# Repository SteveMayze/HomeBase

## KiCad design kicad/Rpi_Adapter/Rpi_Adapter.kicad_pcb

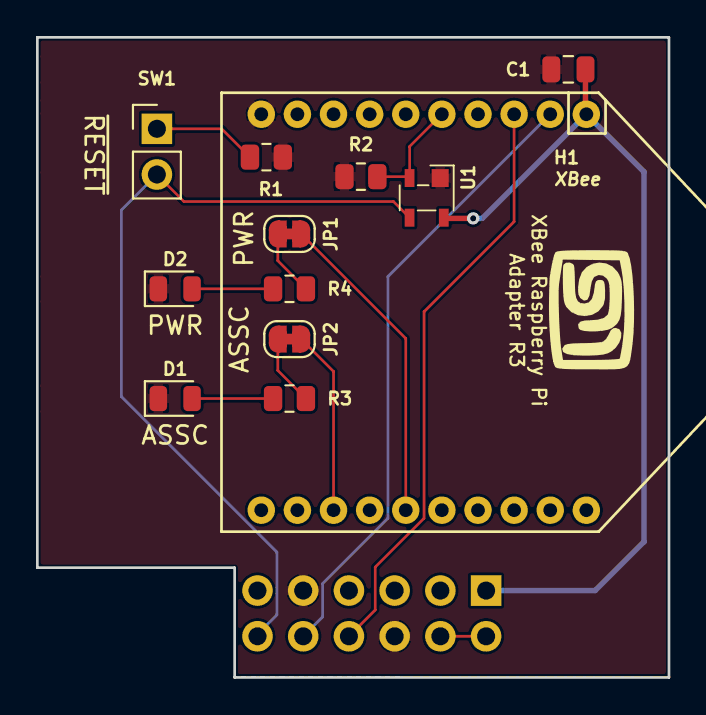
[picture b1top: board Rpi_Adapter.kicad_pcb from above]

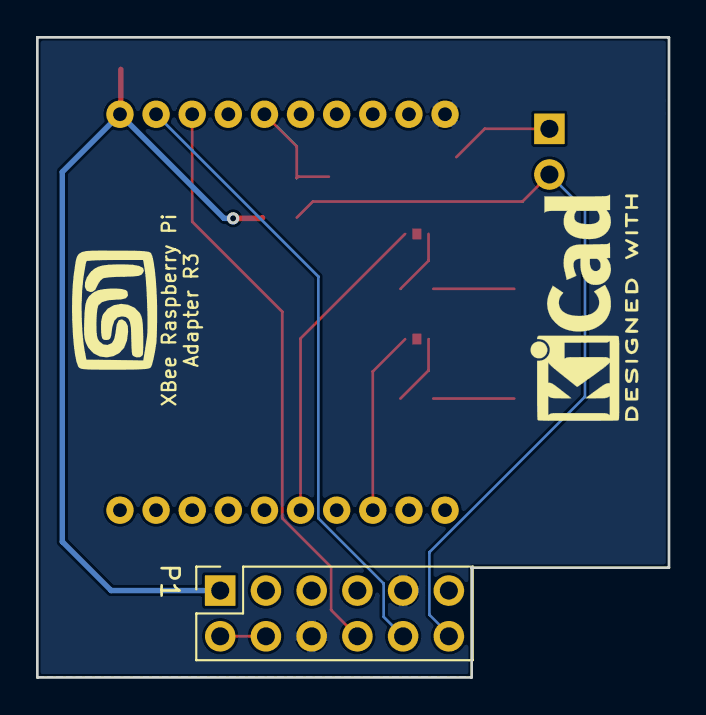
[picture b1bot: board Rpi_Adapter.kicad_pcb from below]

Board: 2 copper layers, 35.1 x 35.6 mm, 18 parts (4 on the bottom side), 14 nets.

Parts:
Brd1: XBee Board; Board Ref
Brd2: Raspberry Pi Zero; Board Ref
C1: 100nF; C_0805_2012Metric
D1, D2: LED; LED_0805_2012Metric
H1: DIGI_XBEE; XBEE_S2C
JP1: ASSOCIATE; SolderJumper-2_P1.3mm_Bridged_RoundedPad1.0x1.5mm
JP2: ON; SolderJumper-2_P1.3mm_Bridged_RoundedPad1.0x1.5mm
Lg1, Lg3: logo; MyBasic_rounded_50_1
Lg2: KiCad; KiCad-Logo2_6mm_SilkScreen
P1: Raspberry PI; Socket_Strip_Straight_2x06_Pitch2.54mm
R1, R2: 100kΩ; R_0805_2012Metric
R3, R4: 680Ω; R_0805_2012Metric
SW1: SW_Push; PinHeader_1x02_P2.54mm_Vertical
U1: SGM811; SGM811B

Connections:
/3V3: C1.1, H1.1, P1.1, U1.4
/5V: P1.2, P1.4
/GPIO_18: P1.12, SW1.2, U1.3
/UART0_Rx: H1.2, P1.10
/UART0_Tx: H1.3, P1.8
/~RESET: H1.5, R2.1, U1.2
GND: C1.2, D1.1, D2.1, H1.10, P1.6, P1.9, R1.2, R2.2, U1.1
unnamed: D1.2, R3.2
unnamed: D2.2, R4.2
unnamed: H1.13, JP2.1
unnamed: H1.15, JP1.1
unnamed: JP1.2, R4.1
unnamed: JP2.2, R3.1
unnamed: R1.1, SW1.1

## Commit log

2017-08-15 Created the layout and submitted to OSH Park
2017-08-19 included the field device symbols
2021-08-30 Ads a SGM811 and reference to a shared library
2021-09-01 Updated the 3d view and a new layout
2021-09-03 Initial routing
2021-09-03 Completed the layout and routing, Sent to OSH Park
